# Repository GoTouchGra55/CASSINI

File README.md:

# 

### A **rocket flight computer** designed for a self landing rocket.

## Overview

I had a  of fun designing this project, though there may still be a few mistakes here and there, so forgive me for that

Feel free to suggest improvements, modify the design, or contribute your own ideas to the project as well!

See [Schematics](KiCAD/CASSINI.pdf)

## Extra Info

1. **Use a 2s-3s LiPo battery** if you decide to use this board in your project. **Discard the battery if it smells "funny".**

2. **Check for any damage on the pcb** as it can be the reason for a **catastrophic failure**.

3. **USE A 915MHz SMA ANTENNA ONLY!** Others will work fine but you'll spend a while wondering about the poor range.

## Firmware Flashing Instructions

### 1. Clone the repository

```bash
git clone git@github.com:GoTouchGra55/CASSINI.git
```

### 2. Open the project in a code editor

Navigate into the firmware directory. For VS Code users:

```bash
cd CASSINI
code .
```

### 3. Edit the code

You have all the freedom to implement your own new features. Infact, I encourage you to do so.

Just be sure to add your drivers to the `CMakeLists.txt` file or you'll be stuck with a nasty build error and wonder why your code won't work.

_(Speaking from experience)_

### 4. Build the firmware

```bash
cmake --preset Debug
cmake --build --preset Debug
```

### 5. Connect the ST-Link debugger

Connect the pins according to the silkscreen and the debugger labels.

Note: You can skip the 3.3V if your board is powered by an external power source.

### 6. Flash the firmware

With the ST-Link connected, press the Debug button in VS Code.

Cortex-Debug will launch the debugger and program the generated .elf file into the STM32's internal flash.

Once the firmware has been flashed, you can stop the debugging session.

### 7. Disconnect the ST-Link

You can now disconnect the ST-Link from the CASSINI board before testing standalone operation.

The ST-Link is connected to the STM32's debug and reset circuitry. Leaving it connected can affect the NRST line and prevent the board from operating correctly when powered independently.

I faced this error during the final phases of development and thought that it was a hardware error from my part, but really, it's the debugger. So, always remove before testing standalone operation.

### 8. Power the board

Disconnect USB and power CASSINI from a suitable power source.

The STM32 should now boot directly from its internal flash and execute the newly flashed firmware.

## Bill Of Materials

| # | Component / Item | Specifications | Qty. | Price (USD) |
|---:|---|---|---:|---:|
| 1 | KF350 Terminal Blocks | 3-pin, 3.5 mm pitch, 10 pcs | 1  | $4.03 |
| 2 | KF350 Terminal Blocks | 2-pin, 3.5 mm pitch, 10 pcs | 1  | $3.67 |
| 3 | SMD Resistor Assortment | 660 pcs, mixed packages and values | 1  | $3.85 |
| 4 | SMD Resistor Assortment | 1,500 pcs, 0603, 60 values | 1  | $6.40 |
| 5 | SMD Ceramic Capacitor Assortment | 2,500 pcs, 50 values, mixed packages | 1  | ~$9.15 |
| 6 | SMD Ceramic Capacitor Assortment | Mixed packages and quantities | 1  | $6.54 |
| 7 | STM32F405RGT6 Microcontroller | LQFP-64 | 1 pc | $6.09 |
| 8 | CD54 SMD Power Inductor Assortment | 20 pcs, assorted inductance values | 1  | $4.43 |
| 9 | JLCPCB PCB Fabrication & Assembly | PCB manufacturing and assembly order | 1 order | $245.02 |
| | **Daraz Merchandise Subtotal** | | | **$44.16** |
| | Daraz Discount | | | −$1.77 |
| | Daraz Shipping | | | $2.38 |
| | **Daraz Total** | | | **$46.54** |
| | **JLCPCB Total** | | | **$245.02** |
| | **GRAND TOTAL** | | | **$291.56** |

### See [Gerber File](KiCAD/production/CASSINI.zip)

## License

### MIT License - see [LICENSE](LICENSE)

## Author

### **Shaurya Tamang**

Contact: [Email](shauryatamang.dev@gmail.com)

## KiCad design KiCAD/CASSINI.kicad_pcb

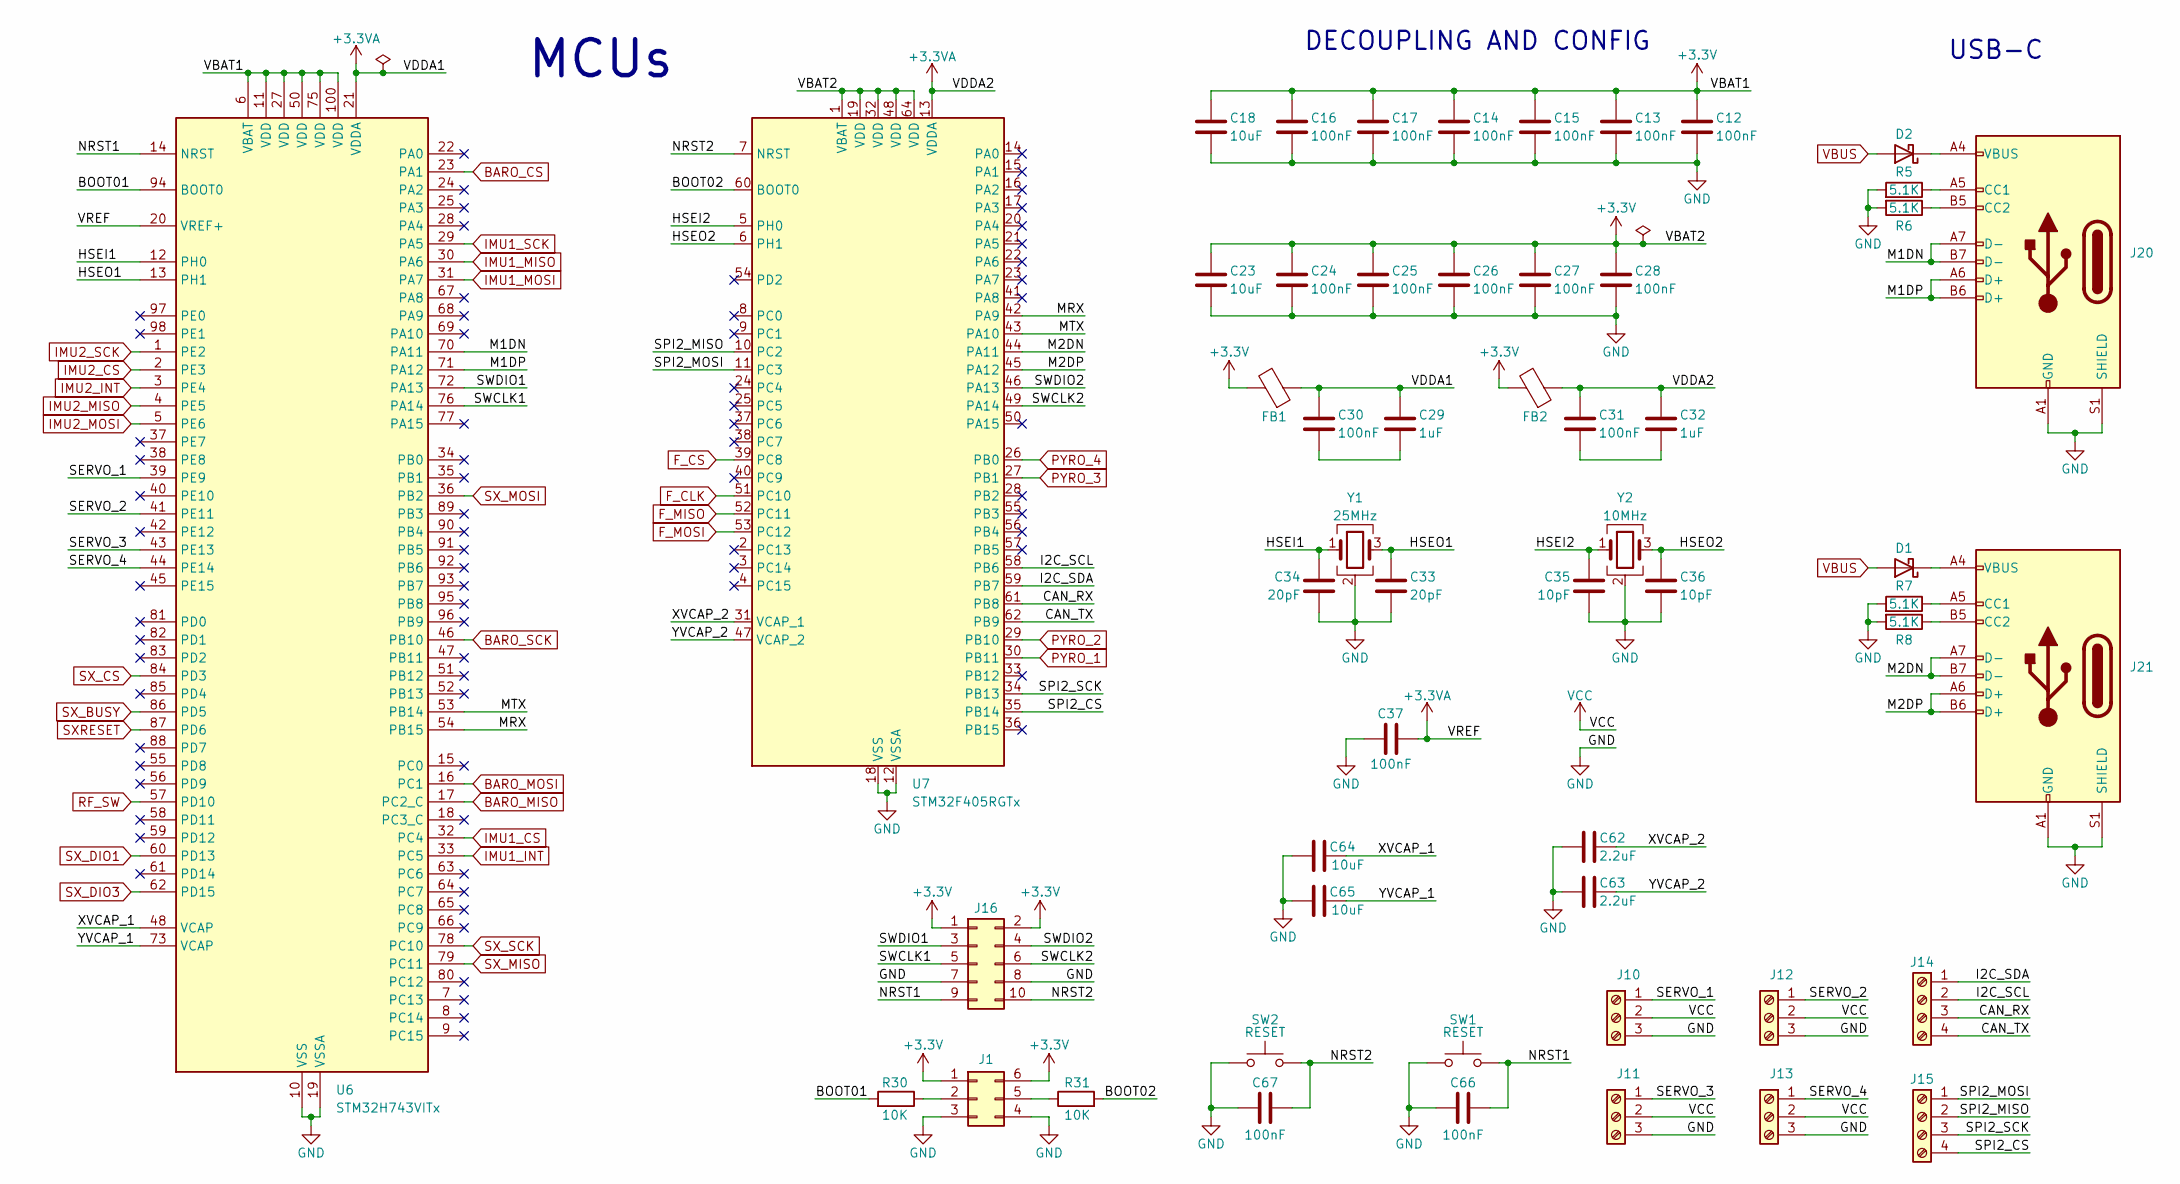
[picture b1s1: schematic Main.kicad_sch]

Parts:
C12, C13, C14, C15, C16, C17, C24, C25, C26, C27, C28, C30, C31, C37, C66, C67: 100nF; C_0402_1005Metric
C18, C23, C64, C65: 10uF; C_0603_1608Metric
C29, C32: 1uF; C_0603_1608Metric
C33, C34: 20pF; C_0402_1005Metric
C35, C36: 10pF; C_0402_1005Metric
C62, C63: 2.2uF; C_0603_1608Metric
D1, D2: D_Schottky; D_SOD-123
FB1, FB2: FerriteBead; C_0603_1608Metric
J1: Conn_02x03_Counter_Clockwise; PinHeader_2x03_P2.54mm_Vertical
J10, J11, J12, J13: Screw_Terminal_01x03; TerminalBlock_Phoenix_MKDS-1-3-3.81_1x03_P3.81mm_Horizontal
J14, J15: Screw_Terminal_01x04; TerminalBlock_Phoenix_MKDS-1-4-3.81_1x04_P3.81mm_Horizontal
J16: Conn_02x05_Counter_Clockwise; PinHeader_2x05_P2.54mm_Vertical
J20, J21: USB_C_Receptacle_USB2.0_14P; USB_C_Receptacle_HRO_TYPE-C-31-M-12
R5, R6, R7, R8: 5.1K; R_0402_1005Metric
R30, R31: 10K; R_0603_1608Metric
SW1, SW2: RESET; SW_Push_SPST_NO_Alps_SKRK
U6: STM32H743VITx; LQFP-100_14x14mm_P0.5mm
U7: STM32F405RGTx; LQFP-64_10x10mm_P0.5mm
Y1: 25MHz; Crystal_SMD_3225-4Pin_3.2x2.5mm
Y2: 10MHz; Crystal_SMD_3225-4Pin_3.2x2.5mm

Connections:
+3.3V: C12.1, C13.1, C14.1, C15.1, C16.1, C17.1, C18.1, C23.1, C24.1, C25.1, C26.1, C27.1, C28.1, FB1.2, FB2.2, J1.1, J1.6, J16.1, J16.2, U6.6 (VBAT), U6.11 (VDD), U6.27 (VDD), U6.50 (VDD), U6.75 (VDD), U6.100 (VDD), U7.1 (VBAT), U7.19 (VDD), U7.32 (VDD), U7.48 (VDD), U7.64 (VDD); also elsewhere on the board
+3.3VA: C29.1, C30.1, C31.1, C32.1, C37.2, FB1.1, FB2.1, U6.20 (VREF+), U6.21 (VDDA), U7.13 (VDDA)
/Main/BOOT01: R30.2, U6.94 (BOOT0)
/Main/BOOT02: R31.2, U7.60 (BOOT0)
/Main/CAN_RX: J14.3, U7.61 (PB8)
/Main/CAN_TX: J14.4, U7.62 (PB9)
/Main/HSEI1: C34.1, U6.12 (PH0), Y1.1
/Main/HSEI2: C35.1, U7.5 (PH0), Y2.1
/Main/HSEO1: C33.1, U6.13 (PH1), Y1.3
/Main/HSEO2: C36.1, U7.6 (PH1), Y2.3
/Main/I2C_SCL: J14.2, U7.58 (PB6)
/Main/I2C_SDA: J14.1, U7.59 (PB7)
/Main/M1DN: J20.A7 (D-), J20.B7 (D-), U6.70 (PA11)
/Main/M1DP: J20.A6 (D+), J20.B6 (D+), U6.71 (PA12)
/Main/M2DN: J21.A7 (D-), J21.B7 (D-), U7.44 (PA11)
/Main/M2DP: J21.A6 (D+), J21.B6 (D+), U7.45 (PA12)
/Main/MRX: U6.54 (PB15), U7.42 (PA9)
/Main/MTX: U6.53 (PB14), U7.43 (PA10)
/Main/NRST1: C66.2, J16.9, SW1.2, U6.14 (NRST)
/Main/NRST2: C67.2, J16.10, SW2.2, U7.7 (NRST)
/Main/SERVO_1: J10.1, U6.39 (PE9)
/Main/SERVO_2: J12.1, U6.41 (PE11)
/Main/SERVO_3: J11.1, U6.43 (PE13)
/Main/SERVO_4: J13.1, U6.44 (PE14)
/Main/SPI2_CS: J15.4, U7.35 (PB14)
/Main/SPI2_MISO: J15.2, U7.10 (PC2)
/Main/SPI2_MOSI: J15.1, U7.11 (PC3)
/Main/SPI2_SCK: J15.3, U7.34 (PB13)
/Main/SWCLK1: J16.5, U6.76 (PA14)
/Main/SWCLK2: J16.6, U7.49 (PA14)
/Main/SWDIO1: J16.3, U6.72 (PA13)
/Main/SWDIO2: J16.4, U7.46 (PA13)
/Main/XVCAP_1: C64.2, U6.48 (VCAP)
/Main/XVCAP_2: C62.2, U7.31 (VCAP_1)
/Main/YVCAP_1: C65.2, U6.73 (VCAP)
/Main/YVCAP_2: C63.2, U7.47 (VCAP_2)
BARO_CS: U6.23 (PA1); also elsewhere on the board
BARO_MISO: U6.17 (PC2_C); also elsewhere on the board
BARO_MOSI: U6.16 (PC1); also elsewhere on the board
BARO_SCK: U6.46 (PB10); also elsewhere on the board
F_CLK: U7.51 (PC10); also elsewhere on the board
F_CS: U7.39 (PC8); also elsewhere on the board
F_MISO: U7.52 (PC11); also elsewhere on the board
F_MOSI: U7.53 (PC12); also elsewhere on the board
GND: C12.2, C13.2, C14.2, C15.2, C16.2, C17.2, C18.2, C23.2, C24.2, C25.2, C26.2, C27.2, C28.2, C33.2, C34.2, C35.2, C36.2, C37.1, C62.1, C63.1, C64.1, C65.1, C66.1, C67.1, J1.3, J1.4, J10.3, J11.3, J12.3, J13.3, J16.7, J16.8, J20.A1 (GND), J20.A12 (GND), J20.B1 (GND), J20.B12 (GND), J20.S1 (SHIELD), J21.A1 (GND), J21.A12 (GND), J21.B1 (GND), J21.B12 (GND), J21.S1 (SHIELD), R5.2, R6.2, R7.2, R8.2, SW1.1, SW2.1, U6.10 (VSS), U6.19 (VSSA), U6.26 (VSS), U6.49 (VSS), U6.74 (VSS), U6.99 (VSS), U7.12 (VSSA), U7.18 (VSS), U7.63 (VSS), Y1.2 (G), Y1.4 (G), Y2.2 (G), Y2.4 (G); also elsewhere on the board
IMU1_CS: U6.32 (PC4); also elsewhere on the board
IMU1_INT: U6.33 (PC5); also elsewhere on the board
IMU1_MISO: U6.30 (PA6); also elsewhere on the board
IMU1_MOSI: U6.31 (PA7); also elsewhere on the board
IMU1_SCK: U6.29 (PA5); also elsewhere on the board
IMU2_CS: U6.2 (PE3); also elsewhere on the board
IMU2_INT: U6.3 (PE4); also elsewhere on the board
IMU2_MISO: U6.4 (PE5); also elsewhere on the board
IMU2_MOSI: U6.5 (PE6); also elsewhere on the board
IMU2_SCK: U6.1 (PE2); also elsewhere on the board
unnamed: C29.2, C30.2
unnamed: C31.2, C32.2
unnamed: D1.1 (K), J21.A4 (VBUS), J21.A9 (VBUS), J21.B4 (VBUS), J21.B9 (VBUS)
unnamed: D2.1 (K), J20.A4 (VBUS), J20.A9 (VBUS), J20.B4 (VBUS), J20.B9 (VBUS)
unnamed: J1.2, R30.1
unnamed: J1.5, R31.1
unnamed: J20.A5 (CC1), R5.1
unnamed: J20.B5 (CC2), R6.1
unnamed: J21.A5 (CC1), R7.1
unnamed: J21.B5 (CC2), R8.1
PYRO_1: U7.30 (PB11); also elsewhere on the board
PYRO_2: U7.29 (PB10); also elsewhere on the board
PYRO_3: U7.27 (PB1); also elsewhere on the board
PYRO_4: U7.26 (PB0); also elsewhere on the board
RF_SW: U6.57 (PD10); also elsewhere on the board
SXRESET: U6.87 (PD6); also elsewhere on the board
SX_BUSY: U6.86 (PD5); also elsewhere on the board
SX_CS: U6.84 (PD3); also elsewhere on the board
SX_DIO1: U6.60 (PD13); also elsewhere on the board
SX_DIO3: U6.62 (PD15); also elsewhere on the board
SX_MISO: U6.79 (PC11); also elsewhere on the board
SX_MOSI: U6.36 (PB2); also elsewhere on the board
SX_SCK: U6.78 (PC10); also elsewhere on the board
VBUS: D1.2 (A), D2.2 (A); also elsewhere on the board
VCC: J10.2, J11.2, J12.2, J13.2; also elsewhere on the board

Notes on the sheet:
USB-C
MCUs
DECOUPLING AND CONFIG

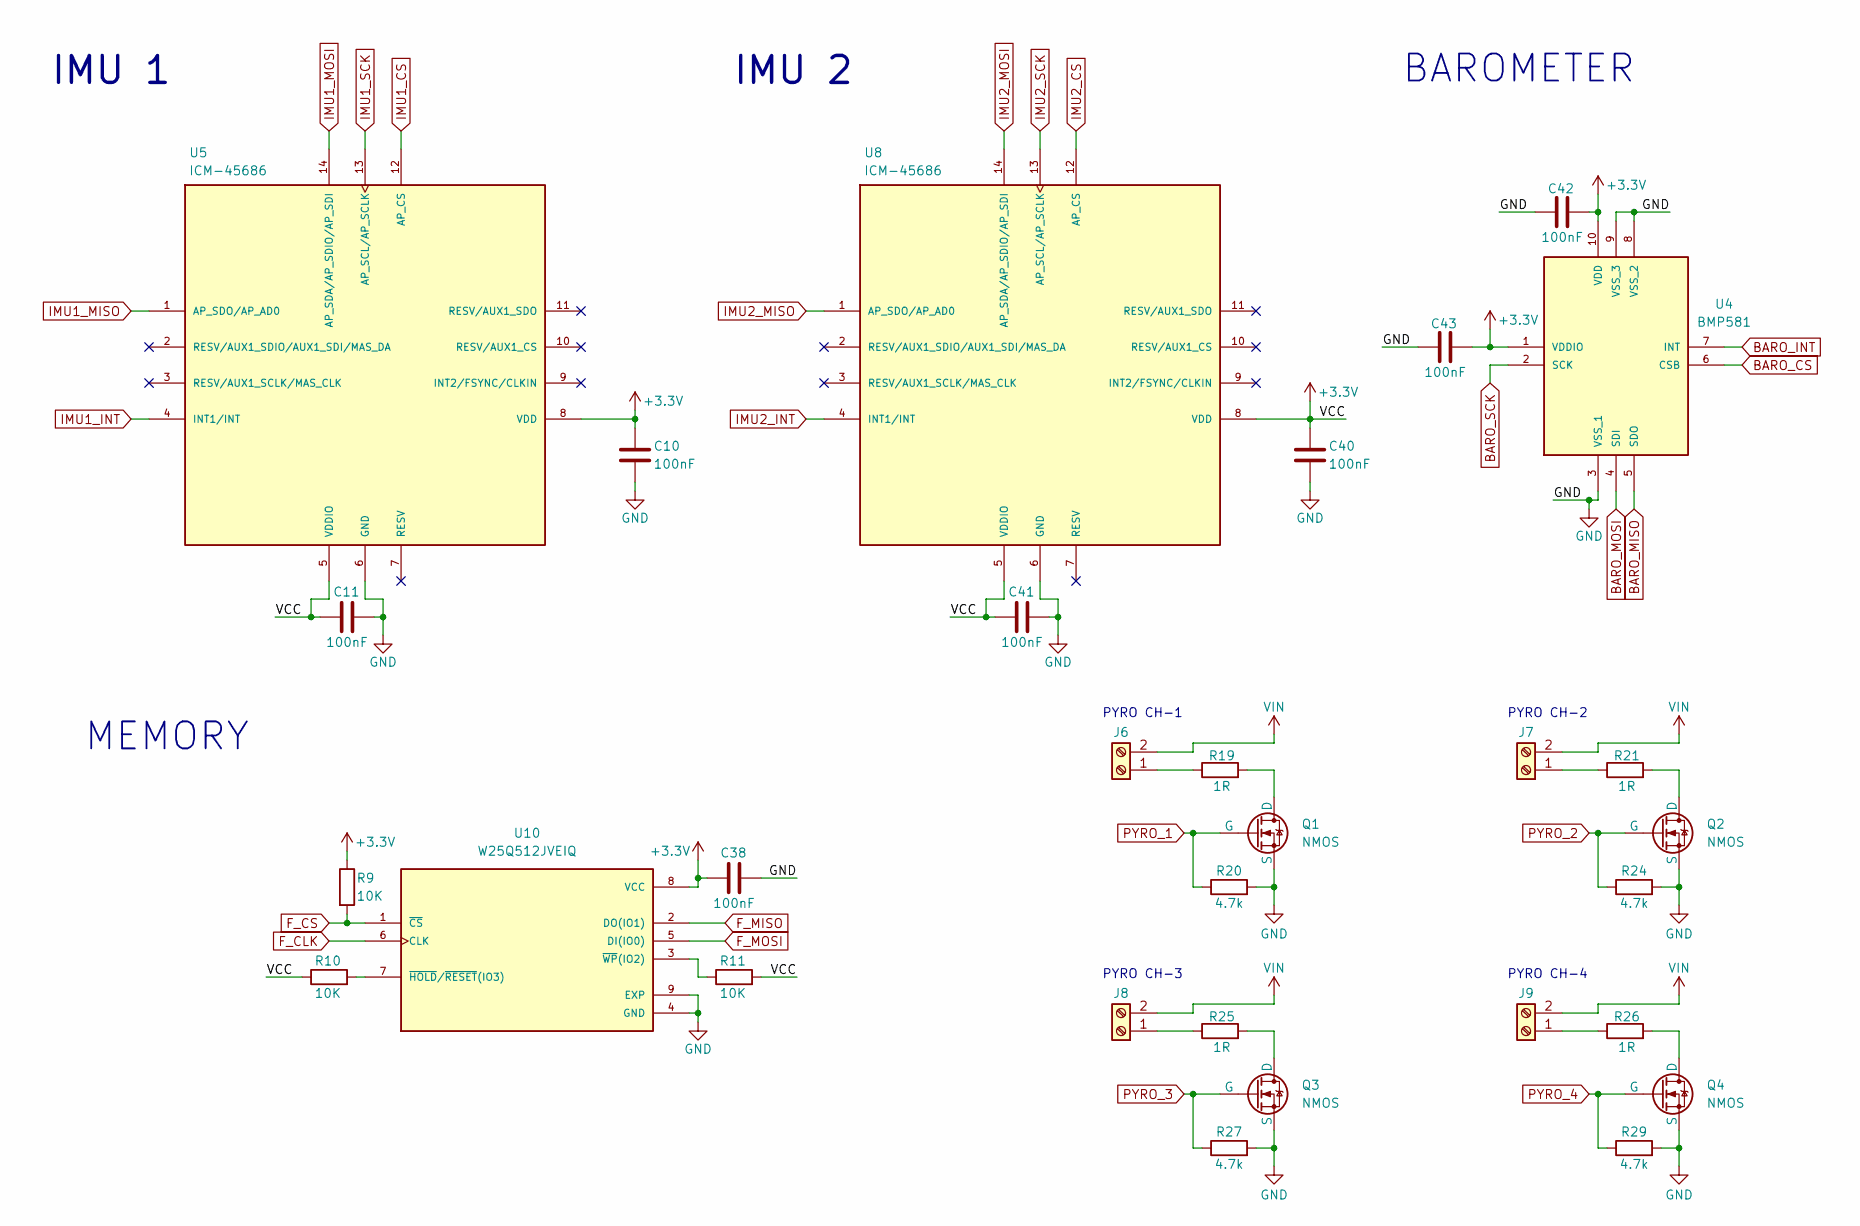
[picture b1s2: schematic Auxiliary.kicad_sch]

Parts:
C10, C11, C38, C40, C41, C42, C43: 100nF; C_0402_1005Metric
J6, J7, J8, J9: Screw_Terminal_01x02; TerminalBlock_Phoenix_MKDS-1-2-3.81_1x02_P3.81mm_Horizontal
Q1, Q2, Q3, Q4: NMOS; TRANS_IRLML6344TRPBF
R9, R10, R11: 10K; R_0603_1608Metric
R19, R21, R25, R26: 1R; R_0402_1005Metric
R20, R24, R27, R29: 4.7k; R_0402_1005Metric
U4: BMP581; Manufacturer_Part_Number BMP581
U5, U8: ICM-45686; IC_ICM-45686; PARTREV 0.2
U10: W25Q512JVEIQ; SON127P600X800X80-9N; PARTREV G

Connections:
+3.3V: C10.1, C11.2, C38.2, C40.1, C41.2, C42.2, C43.2, R9.1, R10.1, R11.2, U4.1 (VDDIO), U4.10 (VDD), U5.5 (VDDIO), U5.8 (VDD), U8.5 (VDDIO), U8.8 (VDD), U10.8 (VCC); also elsewhere on the board
BARO_CS: U4.6 (CSB); also elsewhere on the board
BARO_INT: U4.7 (INT)
BARO_MISO: U4.5 (SDO); also elsewhere on the board
BARO_MOSI: U4.4 (SDI); also elsewhere on the board
BARO_SCK: U4.2 (SCK); also elsewhere on the board
F_CLK: U10.6 (CLK); also elsewhere on the board
F_CS: R9.2, U10.1 (~CS); also elsewhere on the board
F_MISO: U10.2 (DO(IO1)); also elsewhere on the board
F_MOSI: U10.5 (DI(IO0)); also elsewhere on the board
GND: C10.2, C11.1, C38.1, C40.2, C41.1, C42.1, C43.1, Q1.3 (S), Q2.3 (S), Q3.3 (S), Q4.3 (S), R20.2, R24.2, R27.2, R29.2, U4.3 (VSS_1), U4.8 (VSS_2), U4.9 (VSS_3), U5.6 (GND), U8.6 (GND), U10.4 (GND), U10.9 (EXP); also elsewhere on the board
IMU1_CS: U5.12 (AP_CS); also elsewhere on the board
IMU1_INT: U5.4 (INT1/INT); also elsewhere on the board
IMU1_MISO: U5.1 (AP_SDO/AP_AD0); also elsewhere on the board
IMU1_MOSI: U5.14 (AP_SDA/AP_SDIO/AP_SDI); also elsewhere on the board
IMU1_SCK: U5.13 (AP_SCL/AP_SCLK); also elsewhere on the board
IMU2_CS: U8.12 (AP_CS); also elsewhere on the board
IMU2_INT: U8.4 (INT1/INT); also elsewhere on the board
IMU2_MISO: U8.1 (AP_SDO/AP_AD0); also elsewhere on the board
IMU2_MOSI: U8.14 (AP_SDA/AP_SDIO/AP_SDI); also elsewhere on the board
IMU2_SCK: U8.13 (AP_SCL/AP_SCLK); also elsewhere on the board
unnamed: J6.1, R19.1
unnamed: J7.1, R21.1
unnamed: J8.1, R25.1
unnamed: J9.1, R26.1
unnamed: Q1.1 (D), R19.2
unnamed: Q2.1 (D), R21.2
unnamed: Q3.1 (D), R25.2
unnamed: Q4.1 (D), R26.2
unnamed: R10.2, U10.7 (~HOLD/~RESET(IO3))
unnamed: R11.1, U10.3 (~WP(IO2))
PYRO_1: Q1.2 (G), R20.1; also elsewhere on the board
PYRO_2: Q2.2 (G), R24.1; also elsewhere on the board
PYRO_3: Q3.2 (G), R27.1; also elsewhere on the board
PYRO_4: Q4.2 (G), R29.1; also elsewhere on the board
VBUS: J6.2, J7.2, J8.2, J9.2; also elsewhere on the board

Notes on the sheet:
IMU 1
IMU 2
MEMORY
PYRO CH-3
PYRO CH-2
PYRO CH-4
PYRO CH-1
BAROMETER

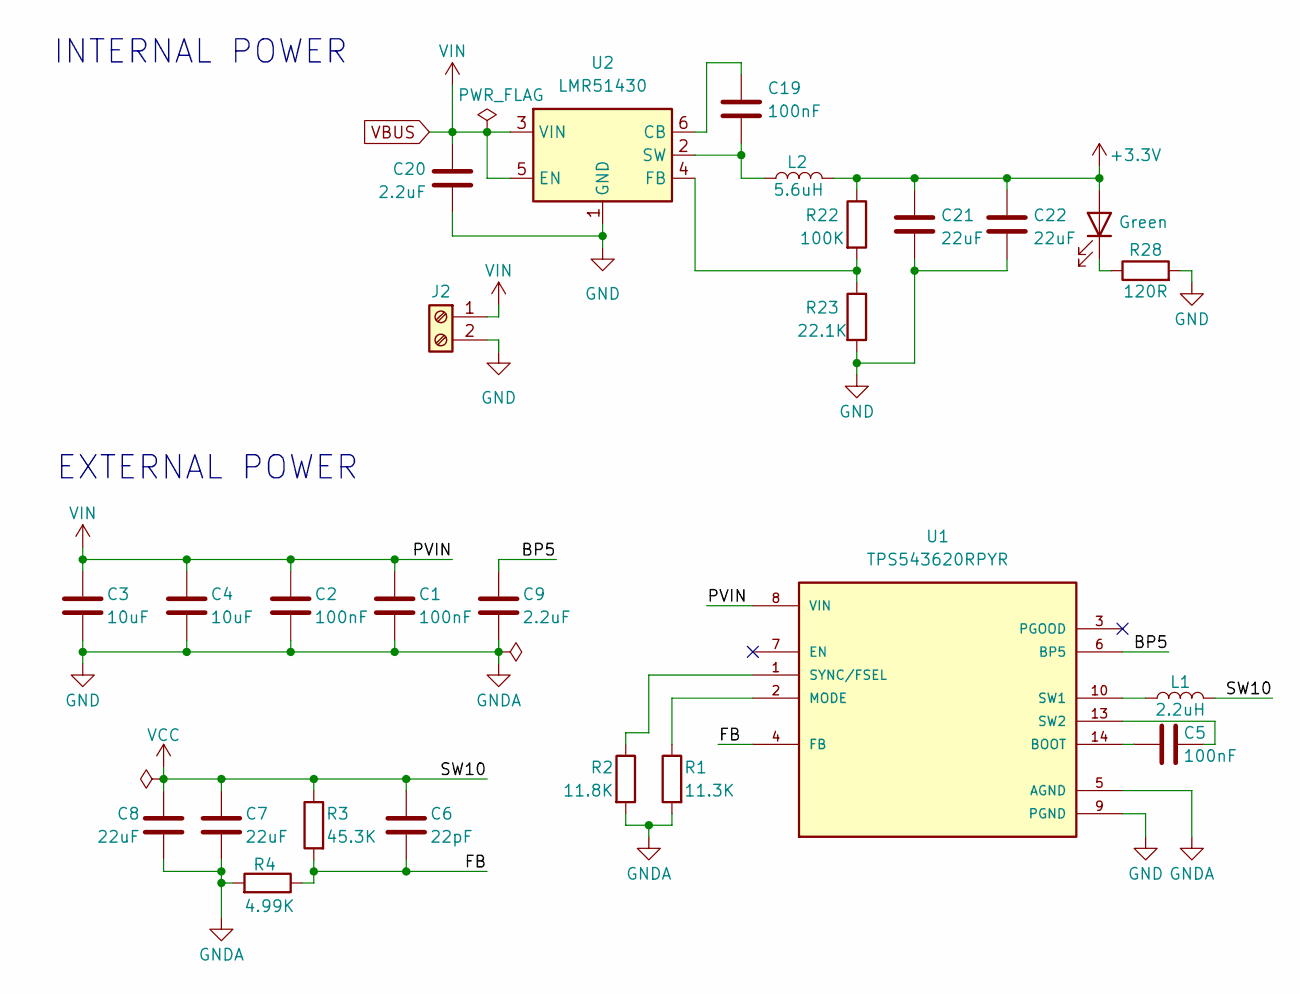
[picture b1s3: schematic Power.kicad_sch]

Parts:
C1, C2, C5, C19: 100nF; C_0402_1005Metric
C3, C4: 10uF; C_0603_1608Metric
C6: 22pF; C_0402_1005Metric
C7, C8: 22uF; C_0402_1005Metric
C9, C20: 2.2uF; C_0603_1608Metric
C21, C22: 22uF; C_0603_1608Metric
Int_Indicator1: Green; LED_0402_1005Metric
J2: Screw_Terminal_01x02; AMASS_XT60-M_1x02_P7.20mm_Vertical
L1: 2.2uH; L_Cenker_CKCS3015
L2: 5.6uH; L_Cenker_CKCS3015
R1: 11.3K; R_0603_1608Metric
R2: 11.8K; R_0603_1608Metric
R3: 45.3K; R_0603_1608Metric
R4: 4.99K; R_0402_1005Metric
R22: 100K; R_0603_1608Metric
R23: 22.1K; R_0603_1608Metric
R28: 120R; R_0402_1005Metric
U1: TPS543620RPYR; PARTREV A
U2: LMR51430; SOT-23-6

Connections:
+3.3V: C21.1, C22.1, Int_Indicator1.2 (A), L2.1, R22.1; also elsewhere on the board
/Power/BP5: C9.1, U1.6 (BP5)
/Power/FB: C6.2, R3.2, R4.1, U1.4 (FB)
GND: C1.2, C2.2, C3.2, C4.2, C7.2, C8.2, C9.2, C20.2, C21.2, C22.2, J2.2, R1.2, R2.2, R4.2, R23.2, R28.2, U1.5 (AGND), U1.9 (PGND), U1.11 (PGND), U2.1 (GND); also elsewhere on the board
unnamed: Int_Indicator1.1 (K), R28.1
unnamed: C5.1, U1.14 (BOOT)
unnamed: R1.1, U1.2 (MODE)
unnamed: L1.1, U1.10 (SW1)
unnamed: C5.2, U1.13 (SW2)
unnamed: R2.1, U1.1 (SYNC/FSEL)
unnamed: C19.1, U2.6 (CB)
unnamed: R22.2, R23.1, U2.4 (FB)
unnamed: C19.2, L2.2, U2.2 (SW)
VBUS: C1.1, C2.1, C3.1, C4.1, C20.1, J2.1, U1.8 (VIN), U1.12 (VIN), U2.3 (VIN), U2.5 (EN); also elsewhere on the board
VCC: C6.1, C7.1, C8.1, L1.2, R3.1; also elsewhere on the board

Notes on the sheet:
INTERNAL POWER
EXTERNAL POWER

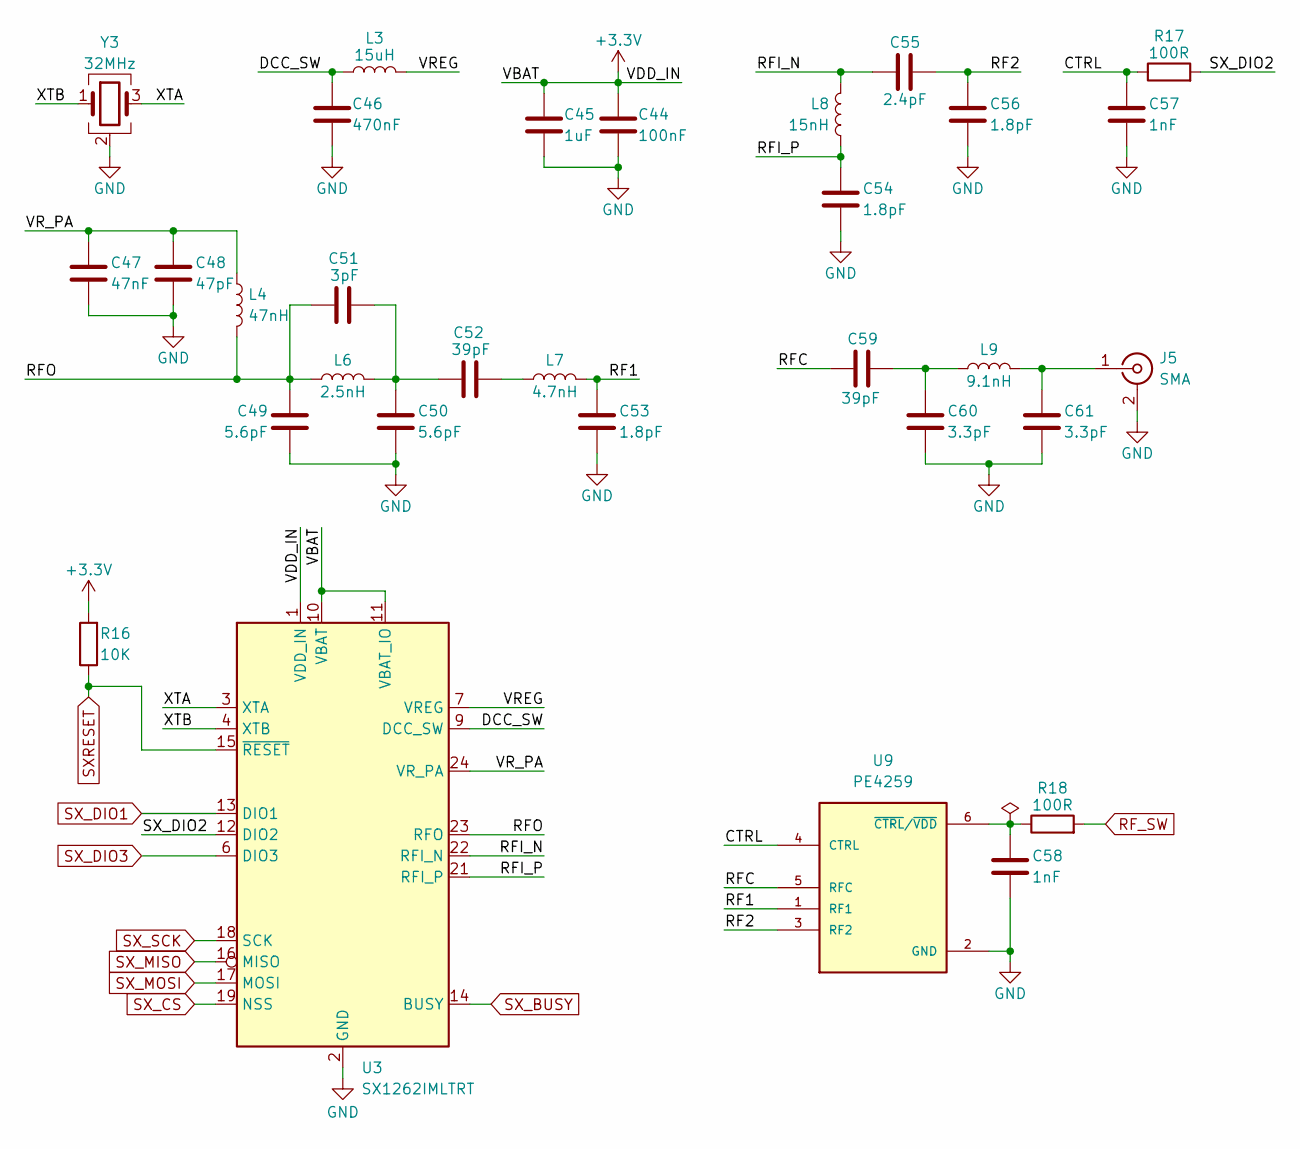
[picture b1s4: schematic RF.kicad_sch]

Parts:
C44: 100nF; C_0402_1005Metric
C45: 1uF; C_0603_1608Metric
C46: 470nF; C_0402_1005Metric
C47: 47nF; C_0402_1005Metric
C48: 47pF; C_0402_1005Metric
C49, C50: 5.6pF; C_0402_1005Metric
C51: 3pF; C_0402_1005Metric
C52, C59: 39pF; C_0402_1005Metric
C53, C54, C56: 1.8pF; C_0402_1005Metric
C55: 2.4pF; C_0402_1005Metric
C57, C58: 1nF; C_0402_1005Metric
C60, C61: 3.3pF; C_0402_1005Metric
J5: SMA; SMA_Amphenol_132134-10_Vertical
L3: 15uH; L_Cenker_CKCS3015
L4: 47nH; L_0402_1005Metric
L6: 2.5nH; L_0402_1005Metric
L7: 4.7nH; L_0402_1005Metric
L8: 15nH; L_0402_1005Metric
L9: 9.1nH; L_0402_1005Metric
R16: 10K; R_0603_1608Metric
R17, R18: 100R; R_0402_1005Metric
U3: SX1262IMLTRT; QFN-24-1EP_4x4mm_P0.5mm_EP2.6x2.6mm
U9: PE4259; SOT65P215X110-6N
Y3: 32MHz; Crystal_SMD_3225-4Pin_3.2x2.5mm

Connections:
+3.3V: C44.1, C45.1, R16.2, U3.1 (VDD_IN), U3.10 (VBAT), U3.11 (VBAT_IO); also elsewhere on the board
/RF/CTRL: C57.1, R17.1, U9.4 (CTRL)
/RF/DCC_SW: C46.1, L3.1, U3.9 (DCC_SW)
/RF/RF1: C53.1, L7.2, U9.1 (RF1)
/RF/RF2: C55.2, C56.1, U9.3 (RF2)
/RF/RFC: C59.1, U9.5 (RFC)
/RF/RFI_N: C55.1, L8.1, U3.22 (RFI_N)
/RF/RFI_P: C54.1, L8.2, U3.21 (RFI_P)
/RF/RFO: C49.1, C51.1, L4.2, L6.1, U3.23 (RFO)
/RF/SX_DIO2: R17.2, U3.12 (DIO2)
/RF/VREG: L3.2, U3.7 (VREG)
/RF/VR_PA: C47.1, C48.1, L4.1, U3.24 (VR_PA)
/RF/XTA: U3.3 (XTA), Y3.3
/RF/XTB: U3.4 (XTB), Y3.1
GND: C44.2, C45.2, C46.2, C47.2, C48.2, C49.2, C50.2, C53.2, C54.2, C56.2, C57.2, C58.2, C60.2, C61.2, J5.2 (Ext), U3.2 (GND), U3.5 (GND), U3.8 (GND), U3.20 (GND), U3.25 (GND), U9.2 (GND), Y3.2 (G), Y3.4 (G); also elsewhere on the board
unnamed: C50.1, C51.2, C52.1, L6.2
unnamed: C52.2, L7.1
unnamed: C59.2, C60.1, L9.1
unnamed: C61.1, J5.1 (In), L9.2
unnamed: C58.1, R18.1, U9.6 (~CTRL/~VDD)
RF_SW: R18.2; also elsewhere on the board
SXRESET: R16.1, U3.15 (~RESET); also elsewhere on the board
SX_BUSY: U3.14 (BUSY); also elsewhere on the board
SX_CS: U3.19 (NSS); also elsewhere on the board
SX_DIO1: U3.13 (DIO1); also elsewhere on the board
SX_DIO3: U3.6 (DIO3); also elsewhere on the board
SX_MISO: U3.16 (MISO); also elsewhere on the board
SX_MOSI: U3.17 (MOSI); also elsewhere on the board
SX_SCK: U3.18 (SCK); also elsewhere on the board

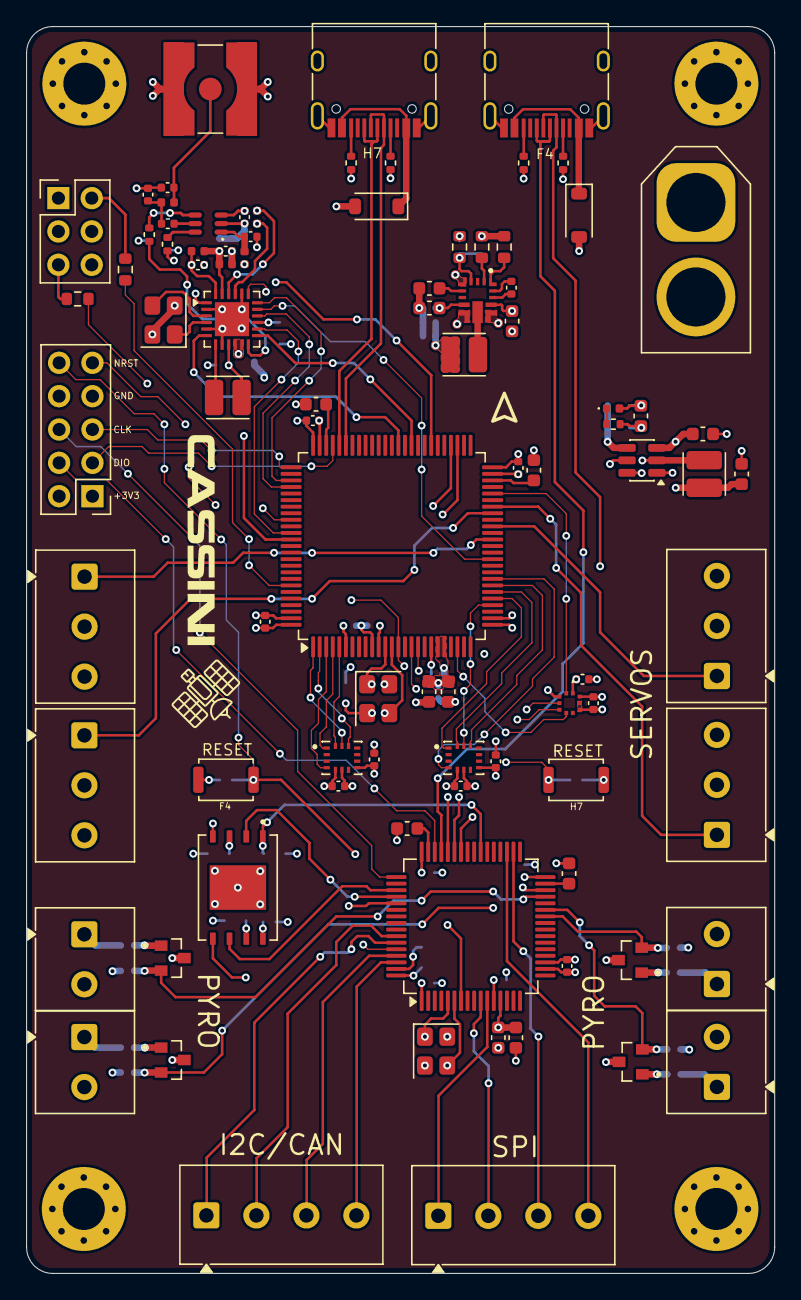
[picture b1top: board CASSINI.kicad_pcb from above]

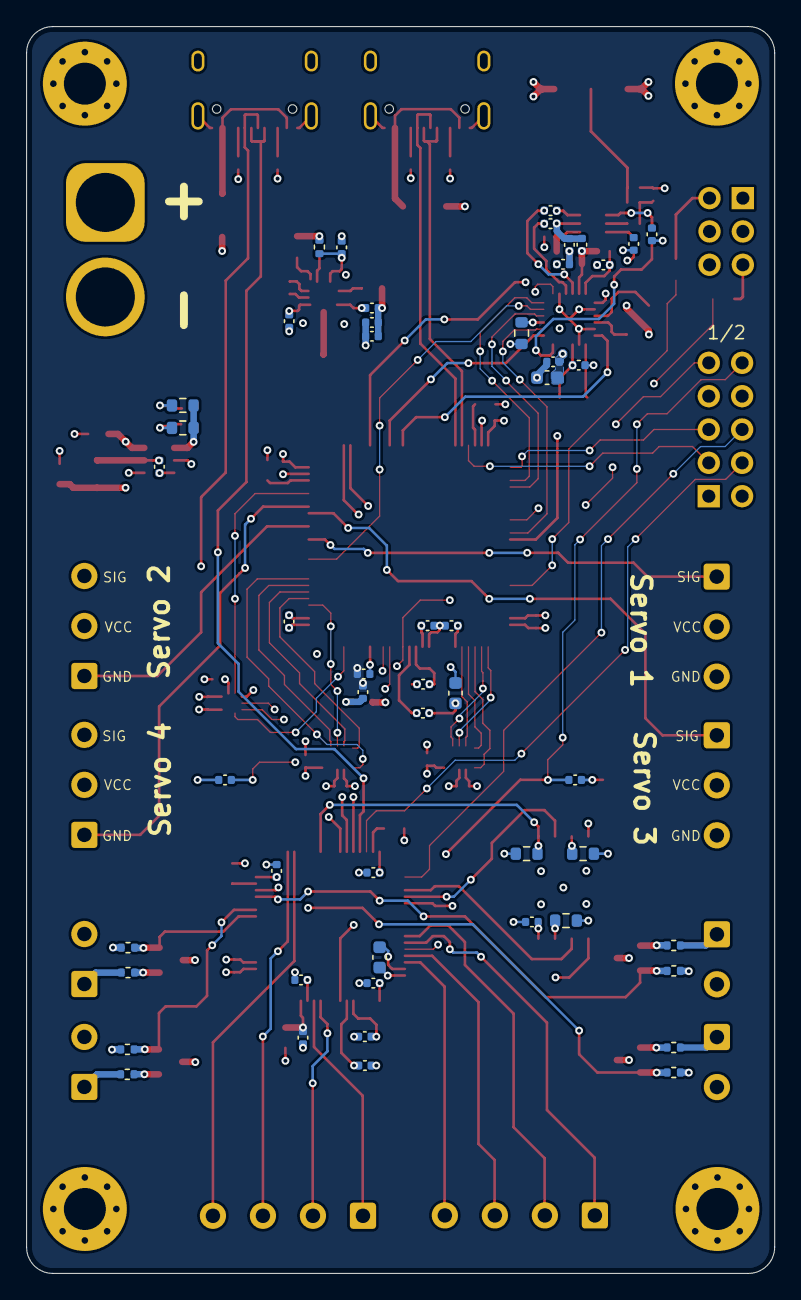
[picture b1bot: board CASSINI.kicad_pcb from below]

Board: 6 copper layers, 57.0 x 95.0 mm, 142 parts (51 on the bottom side), 119 nets.

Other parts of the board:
ww: LOGO

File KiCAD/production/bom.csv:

Designator,Footprint,Quantity,Value,LCSC Part #
"C1, C10, C11, C12, C13, C14, C15, C16, C17, C19, C2, C24, C25, C26, C27, C28, C30, C31, C37, C38, C40, C41, C42, C43, C44, C5, C66, C67",0402,28,100nF,
"C18, C23, C3, C4, C64, C65",0603,6,10uF,
"C20, C62, C63, C9",0603,4,2.2uF,
"C21, C22",0603,2,22uF,
"C29, C32, C45",0603,3,1uF,
"C33, C34",0402,2,20pF,
"C35, C36",0402,2,10pF,
C46,0402,1,470nF,
C47,0402,1,47nF,
C48,0402,1,47pF,
"C49, C50",0402,2,5.6pF,
C51,0402,1,3pF,
"C52, C59",0402,2,39pF,
"C53, C54, C56",0402,3,1.8pF,
C55,0402,1,2.4pF,
"C57, C58",0402,2,1nF,
C6,0402,1,22pF,
"C60, C61",0402,2,3.3pF,
"C7, C8",0402,2,22uF,
"D1, D2",D_SOD-123,2,D_Schottky,
"FB1, FB2",0603,2,FerriteBead,
INT_INDICATOR1,0402,1,Green,
J1,PinHeader_2x03_P2.54mm_Vertical,1,Conn_02x03_Counter_Clockwise,
"J10, J11, J12, J13",TerminalBlock_Phoenix_MKDS-1-3-3.81_1x03_P3.81mm_Horizontal,4,Screw_Terminal_01x03,
"J14, J15",TerminalBlock_Phoenix_MKDS-1-4-3.81_1x04_P3.81mm_Horizontal,2,Screw_Terminal_01x04,
J16,PinHeader_2x05_P2.54mm_Vertical,1,Conn_02x05_Counter_Clockwise,
J2,AMASS_XT60-M_1x02_P7.20mm_Vertical,1,Screw_Terminal_01x02,
"J20, J21",USB_C_Receptacle_HRO_TYPE-C-31-M-12,2,USB_C_Receptacle_USB2.0_14P,
J5,SMA_Amphenol_132134-10_Vertical,1,SMA,
"J6, J7, J8, J9",TerminalBlock_Phoenix_MKDS-1-2-3.81_1x02_P3.81mm_Horizontal,4,Screw_Terminal_01x02,
L1,L_Cenker_CKCS3015,1,2.2uH,
L2,L_Cenker_CKCS3015,1,5.6uH,
L3,L_Cenker_CKCS3015,1,15uH,
L4,0402,1,47nH,
L6,0402,1,2.5nH,
L7,0402,1,4.7nH,
L8,0402,1,15nH,
L9,0402,1,9.1nH,
"Q1, Q2, Q3, Q4",TRANS_IRLML6344TRPBF,4,NMOS,
R1,0603,1,11.3K,
"R10, R11, R16, R30, R31, R9",0603,6,10K,
"R17, R18",0402,2,100R,
"R19, R21, R25, R26",0402,4,1R,
R2,0603,1,11.8K,
"R20, R24, R27, R29",0402,4,4.7k,
R22,0603,1,100K,
R23,0603,1,22.1K,
R28,0402,1,120R,
R3,0603,1,45.3K,
R4,0402,1,4.99K,
"R5, R6, R7, R8",0402,4,5.1K,
"SW1, SW2",SW_Push_SPST_NO_Alps_SKRK,2,RESET,
U1,TPS543620RPYR,1,TPS543620RPYR,
U10,SON127P600X800X80-9N,1,W25Q512JVEIQ,
U2,SOT-23-6,1,LMR51430,
U3,QFN-24-1EP_4x4mm_P0.5mm_EP2.6x2.6mm,1,SX1262IMLTRT,
U4,BMP581,1,BMP581,
"U5, U8",IC_ICM-45686,2,ICM-45686,
U6,LQFP-100_14x14mm_P0.5mm,1,STM32H743VITx,
U7,LQFP-64_10x10mm_P0.5mm,1,STM32F405RGTx,
U9,SOT65P215X110-6N,1,PE4259,
Y1,Crystal_SMD_3225-4Pin_3.2x2.5mm,1,25MHz,
Y2,Crystal_SMD_3225-4Pin_3.2x2.5mm,1,10MHz,
Y3,Crystal_SMD_3225-4Pin_3.2x2.5mm,1,32MHz,

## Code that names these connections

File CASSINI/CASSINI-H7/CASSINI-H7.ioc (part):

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Mcu.Name=STM32H743VITx
Mcu.Package=LQFP100
Mcu.UserName=STM32H743VITx
PA1.GPIOParameters=GPIO_Label
PA1.GPIO_Label=BARO_CS
PA1.Signal=GPIO_Output
PA11.Mode=Host_Only
PA11.Signal=USB_OTG_FS_DM
PA12.Mode=Host_Only
PA12.Signal=USB_OTG_FS_DP
PA13\ (JTMS/SWDIO).Mode=Serial_Wire
PA13\ (JTMS/SWDIO).Signal=DEBUG_JTMS-SWDIO
PA14\ (JTCK/SWCLK).Mode=Serial_Wire
PA14\ (JTCK/SWCLK).Signal=DEBUG_JTCK-SWCLK
PA5.GPIOParameters=GPIO_Label
PA5.GPIO_Label=IMU1_SCK
PA5.Mode=Full_Duplex_Master
PA5.Signal=SPI1_SCK
PA6.GPIOParameters=GPIO_Label
PA6.GPIO_Label=IMU1_MISO
PA6.Mode=Full_Duplex_Master
PA6.Signal=SPI1_MISO
PA7.GPIOParameters=GPIO_Label
PA7.GPIO_Label=IMU1_MOSI
PA7.Mode=Full_Duplex_Master
PA7.Signal=SPI1_MOSI
PB10.GPIOParameters=GPIO_Label
PB10.GPIO_Label=BARO_SCK
PB10.Mode=Full_Duplex_Master
PB10.Signal=SPI2_SCK
PB14.Mode=Asynchronous
PB14.Signal=USART1_TX
PB15.Mode=Asynchronous
PB15.Signal=USART1_RX
PB2.GPIOParameters=GPIO_Label
PB2.GPIO_Label=SX_MOSI
PB2.Mode=Full_Duplex_Master
PB2.Signal=SPI3_MOSI
PC1.GPIOParameters=GPIO_Label
PC1.GPIO_Label=BARO_MOSI
PC1.Mode=Full_Duplex_Master
PC1.Signal=SPI2_MOSI
PC10.GPIOParameters=GPIO_Label
PC10.GPIO_Label=SX_SCK
PC10.Mode=Full_Duplex_Master
PC10.Signal=SPI3_SCK
PC11.GPIOParameters=GPIO_Label
PC11.GPIO_Label=SX_MISO
PC11.Mode=Full_Duplex_Master
PC11.Signal=SPI3_MISO
PC2_C.GPIOParameters=GPIO_Label
PC2_C.GPIO_Label=BARO_MISO
PC2_C.Mode=Full_Duplex_Master
PC2_C.Signal=SPI2_MISO
PC4.GPIOParameters=GPIO_Label
PC4.GPIO_Label=IMU1_CS
PC4.Signal=GPIO_Output
PD10.GPIOParameters=GPIO_Label
PD10.GPIO_Label=RF_SW
PD10.Signal=GPIO_Output
PD13.GPIOParameters=GPIO_Label
PD13.GPIO_Label=SX_DIO1
PD13.Signal=GPXTI13
PD15.GPIOParameters=GPIO_Label
PD15.GPIO_Label=SX_DIO3
PD15.Signal=GPXTI15
PD3.GPIOParameters=GPIO_Label
PD3.GPIO_Label=SX_CS
PD3.Signal=GPIO_Output
PD5.GPIOParameters=GPIO_Label
PD5.GPIO_Label=SX_BUSY
PD5.Signal=GPIO_Input
PD6.GPIOParameters=GPIO_Label
PD6.GPIO_Label=SXRESET
PD6.Signal=GPIO_Output
PE11.GPIOParameters=GPIO_Label
PE11.GPIO_Label=SERVO_2
PE11.Signal=S_TIM1_CH2
PE13.GPIOParameters=GPIO_Label
PE13.GPIO_Label=SERVO_3
PE13.Signal=S_TIM1_CH3
PE14.GPIOParameters=GPIO_Label
PE14.GPIO_Label=SERVO_4
PE14.Signal=S_TIM1_CH4
PE2.GPIOParameters=GPIO_Label
PE2.GPIO_Label=IMU2_SCK
PE2.Mode=Full_Duplex_Master
PE2.Signal=SPI4_SCK
PE3.GPIOParameters=GPIO_Label
PE3.GPIO_Label=IMU2_CS
PE3.Signal=GPIO_Output
PE5.GPIOParameters=GPIO_Label
PE5.GPIO_Label=IMU2_MISO
PE5.Mode=Full_Duplex_Master
PE5.Signal=SPI4_MISO
PE6.GPIOParameters=GPIO_Label
PE6.GPIO_Label=IMU2_MOSI
PE6.Mode=Full_Duplex_Master
PE6.Signal=SPI4_MOSI
PE9.GPIOParameters=GPIO_Label
PE9.GPIO_Label=SERVO_1
PE9.Signal=S_TIM1_CH1
PH0-OSC_IN\ (PH0).Mode=HSE-External-Oscillator
PH0-OSC_IN\ (PH0).Signal=RCC_OSC_IN
PH1-OSC_OUT\ (PH1).Mode=HSE-External-Oscillator
PH1-OSC_OUT\ (PH1).Signal=RCC_OSC_OUT
RCC.SYSCLKFreq_VALUE=75000000
RCC.SYSCLKSource=RCC_SYSCLKSOURCE_PLLCLK
board=custom

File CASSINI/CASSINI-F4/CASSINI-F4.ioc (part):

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Mcu.Name=STM32F405RGTx
Mcu.Package=LQFP64
Mcu.UserName=STM32F405RGTx
PA10.Mode=Asynchronous
PA10.Signal=USART1_RX
PA11.Mode=Host_Only
PA11.Signal=USB_OTG_FS_DM
PA12.Mode=Host_Only
PA12.Signal=USB_OTG_FS_DP
PA13.Mode=Serial_Wire
PA13.Signal=SYS_JTMS-SWDIO
PA14.Mode=Serial_Wire
PA14.Signal=SYS_JTCK-SWCLK
PA5.GPIOParameters=GPIO_Label
PA5.GPIO_Label=SX_SCK
PA5.Mode=Full_Duplex_Master
PA5.Signal=SPI1_SCK
PA6.GPIOParameters=GPIO_Label
PA6.GPIO_Label=SX_MISO
PA6.Mode=Full_Duplex_Master
PA6.Signal=SPI1_MISO
PA7.GPIOParameters=GPIO_Label
PA7.GPIO_Label=SX_MOSI
PA7.Mode=Full_Duplex_Master
PA7.Signal=SPI1_MOSI
PA9.Mode=Asynchronous
PA9.Signal=USART1_TX
PB0.GPIOParameters=GPIO_Label
PB0.GPIO_Label=PYRO_4
PB0.Signal=GPIO_Input
PB1.GPIOParameters=GPIO_Label
PB1.GPIO_Label=PYRO_3
PB1.Signal=GPIO_Output
PB10.GPIOParameters=GPIO_Label
PB10.GPIO_Label=PYRO_2
PB10.Signal=GPIO_Output
PB11.GPIOParameters=GPIO_Label
PB11.GPIO_Label=PYRO_1
PB11.Signal=GPIO_Output
PB13.Mode=Full_Duplex_Master
PB13.Signal=SPI2_SCK
PB14.GPIOParameters=GPIO_Label
PB14.GPIO_Label=SPI2_CS
PB14.Signal=GPIO_Output
PB6.Mode=I2C
PB6.Signal=I2C1_SCL
PB7.Mode=I2C
PB7.Signal=I2C1_SDA
PB8.Mode=CAN_Activate
PB8.Signal=CAN1_RX
PB9.Mode=CAN_Activate
PB9.Signal=CAN1_TX
PC10.GPIOParameters=GPIO_Label
PC10.GPIO_Label=F_SCK
PC10.Mode=Full_Duplex_Master
PC10.Signal=SPI3_SCK
PC11.GPIOParameters=GPIO_Label
PC11.GPIO_Label=F_MISO
PC11.Mode=Full_Duplex_Master
PC11.Signal=SPI3_MISO
PC12.GPIOParameters=GPIO_Label
PC12.GPIO_Label=F_MOSI
PC12.Mode=Full_Duplex_Master
PC12.Signal=SPI3_MOSI
PC2.Mode=Full_Duplex_Master
PC2.Signal=SPI2_MISO
PC3.Mode=Full_Duplex_Master
PC3.Signal=SPI2_MOSI
PC8.GPIOParameters=GPIO_Label
PC8.GPIO_Label=F_CS
PC8.Signal=GPIO_Output
PH0-OSC_IN.Mode=HSE-External-Oscillator
PH0-OSC_IN.Signal=RCC_OSC_IN
PH1-OSC_OUT.Mode=HSE-External-Oscillator
PH1-OSC_OUT.Signal=RCC_OSC_OUT
RCC.HSE_VALUE=25000000
RCC.SYSCLKFreq_VALUE=120000000
RCC.SYSCLKSource=RCC_SYSCLKSOURCE_PLLCLK
board=custom
